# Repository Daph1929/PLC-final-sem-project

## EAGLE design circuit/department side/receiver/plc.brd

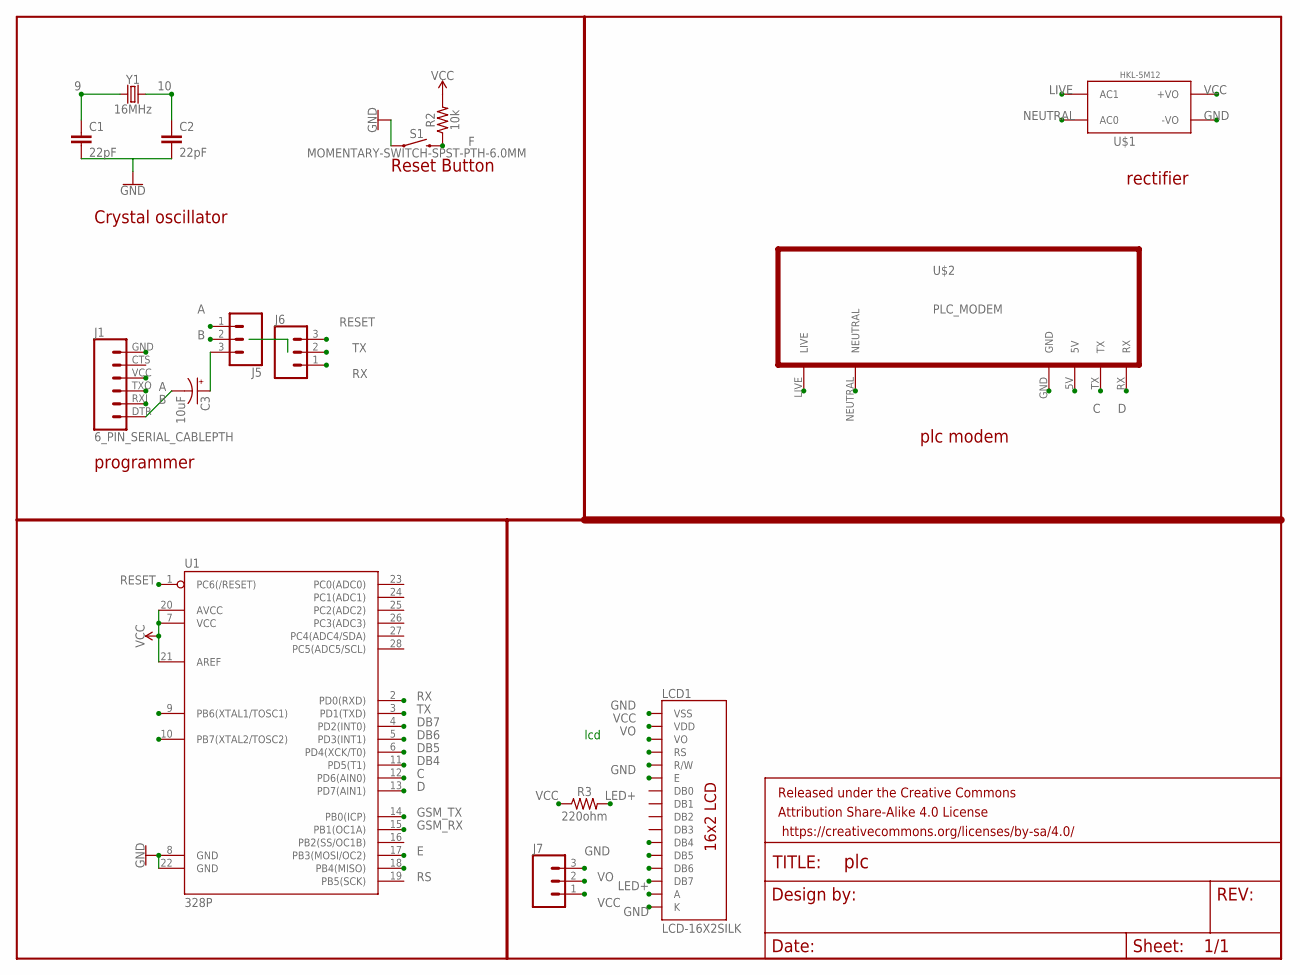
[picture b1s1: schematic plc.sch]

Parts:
C1, C2: 22pF; CAP-PTH-2.54
C3: 10uF; CPOL-RADIAL-2.5MM-5MM
FRAME1: FRAME-LETTERNO_PACKAGE; DUMMY
J1: 6_PIN_SERIAL_CABLEPTH; FTDI_BASIC
J5, J6, J7: CONN_03; 1X03
LCD1: LCD-16X2SILK; LCD-16X2
R2: 10k; AXIAL-0.3
R3: 220ohm; AXIAL-0.3
S1: MOMENTARY-SWITCH-SPST-PTH-6.0MM; TACTILE_SWITCH_PTH_6.0MM
U1: 328P; DIP28
U$1: HKL-5M12; HLK-5M12
U$2: PLC_MODEM; PLC_SUNROM
Y1: 16MHz; HC49US

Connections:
9: C1.1, U1.9 (PB6(XTAL1/TOSC1)), Y1.1
10: C2.1, U1.10 (PB7(XTAL2/TOSC2)), Y1.2
A: J1.TXO (3), J5.1
B: J1.RXI (2), J5.2
C: U1.12 (PD6(AIN0)), U$2.TX
D: U1.13 (PD7(AIN1)), U$2.RX
DB4: LCD1.11 (DB4), U1.11 (PD5(T1))
DB5: LCD1.12 (DB5), U1.6 (PD4(XCK/T0))
DB6: LCD1.13 (DB6), U1.5 (PD3(INT1))
DB7: LCD1.14 (DB7), U1.4 (PD2(INT0))
E: LCD1.6 (E), U1.17 (PB3(MOSI/OC2))
F: R2.P$1 (1), S1.3 (2)
GND: C1.2, C2.2, J1.GND (6), J7.3, LCD1.1 (VSS), LCD1.5 (R/W), LCD1.16 (K), S1.1, U1.8 (GND), U1.22 (GND), U$1.3 (-VO), U$2.GND
GSM_RX: U1.15 (PB1(OC1A))
GSM_TX: U1.14 (PB0(ICP))
LED+: LCD1.15 (A), R3.P$2 (2)
LIVE: U$1.2 (AC1), U$2.LIVE
unnamed: C3.2 (-), J1.DTR (1)
unnamed: C3.1 (+), J5.3
NEUTRAL: U$1.1 (AC0), U$2.NEUTRAL
RESET: J6.3, U1.1 (PC6(/RESET))
RS: LCD1.4 (RS), U1.18 (PB4(MISO))
RX: J6.1, U1.2 (PD0(RXD))
TX: J6.2, U1.3 (PD1(TXD))
VCC: J1.VCC (4), J7.1, LCD1.2 (VDD), R2.P$2 (2), R3.P$1 (1), U1.7 (VCC), U1.20 (AVCC), U1.21 (AREF), U$1.4 (+VO), U$2.5V
VO: J7.2, LCD1.3 (VO)

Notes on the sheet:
Crystal oscillator
Reset Button
lcd
programmer
plc modem
rectifier

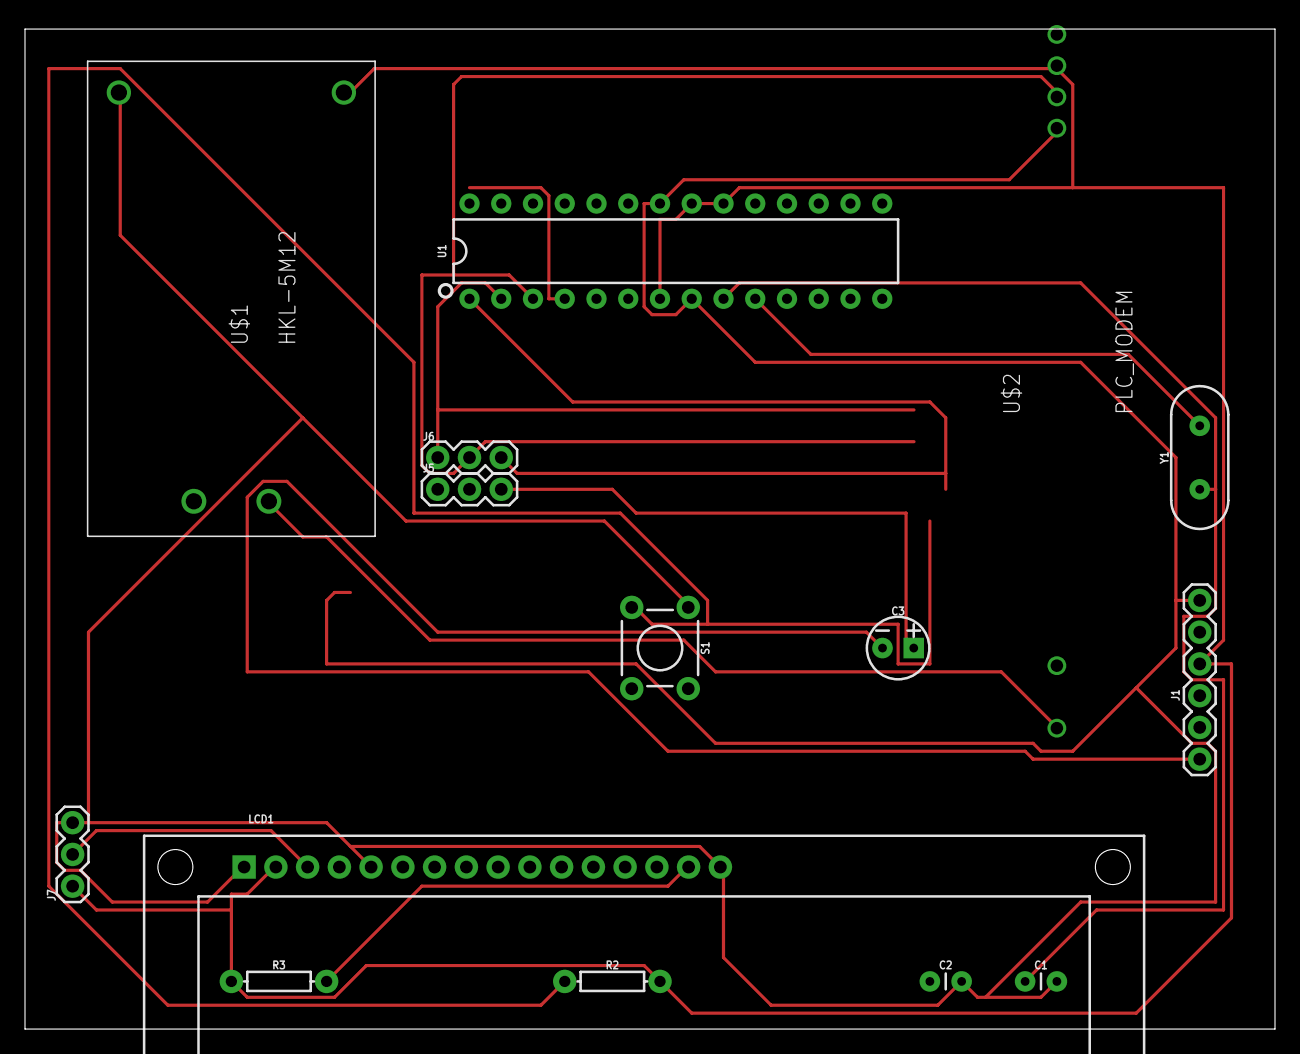
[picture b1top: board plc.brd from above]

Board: 2 copper layers, 100.0 x 80.0 mm, 16 parts (0 on the bottom side), 24 nets.

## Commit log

2017-06-26 plc code
2017-06-27 plc circuit
2017-06-27 plc new change, hopefully the last one
2017-06-29 code for tx updated
2017-06-29 code for tx updated again
2017-06-29 code done, some commenting parts left
2017-06-29 removed nwanted counting folder
2017-06-30 code completed
2017-06-30 circuit explanation
2017-07-10 circuit receiver side added
2017-07-10 done
2017-07-14 rx code lcd part one line arrangement change

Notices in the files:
parts and their libraries:
SparkFun-Capacitors: Licensing: Creative Commons ShareAlike 4.0 International - https://creativecommons.org/licenses/by-sa/4.0
SparkFun-Aesthetics: Released under the Creative Commons Attribution Share-Alike 4.0 License
SparkFun-Aesthetics: https://creativecommons.org/licenses/by-sa/4.0
